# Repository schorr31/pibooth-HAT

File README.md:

# pibooth-HAT
A Raspberry Pi HAT for the pibooth application

### Images

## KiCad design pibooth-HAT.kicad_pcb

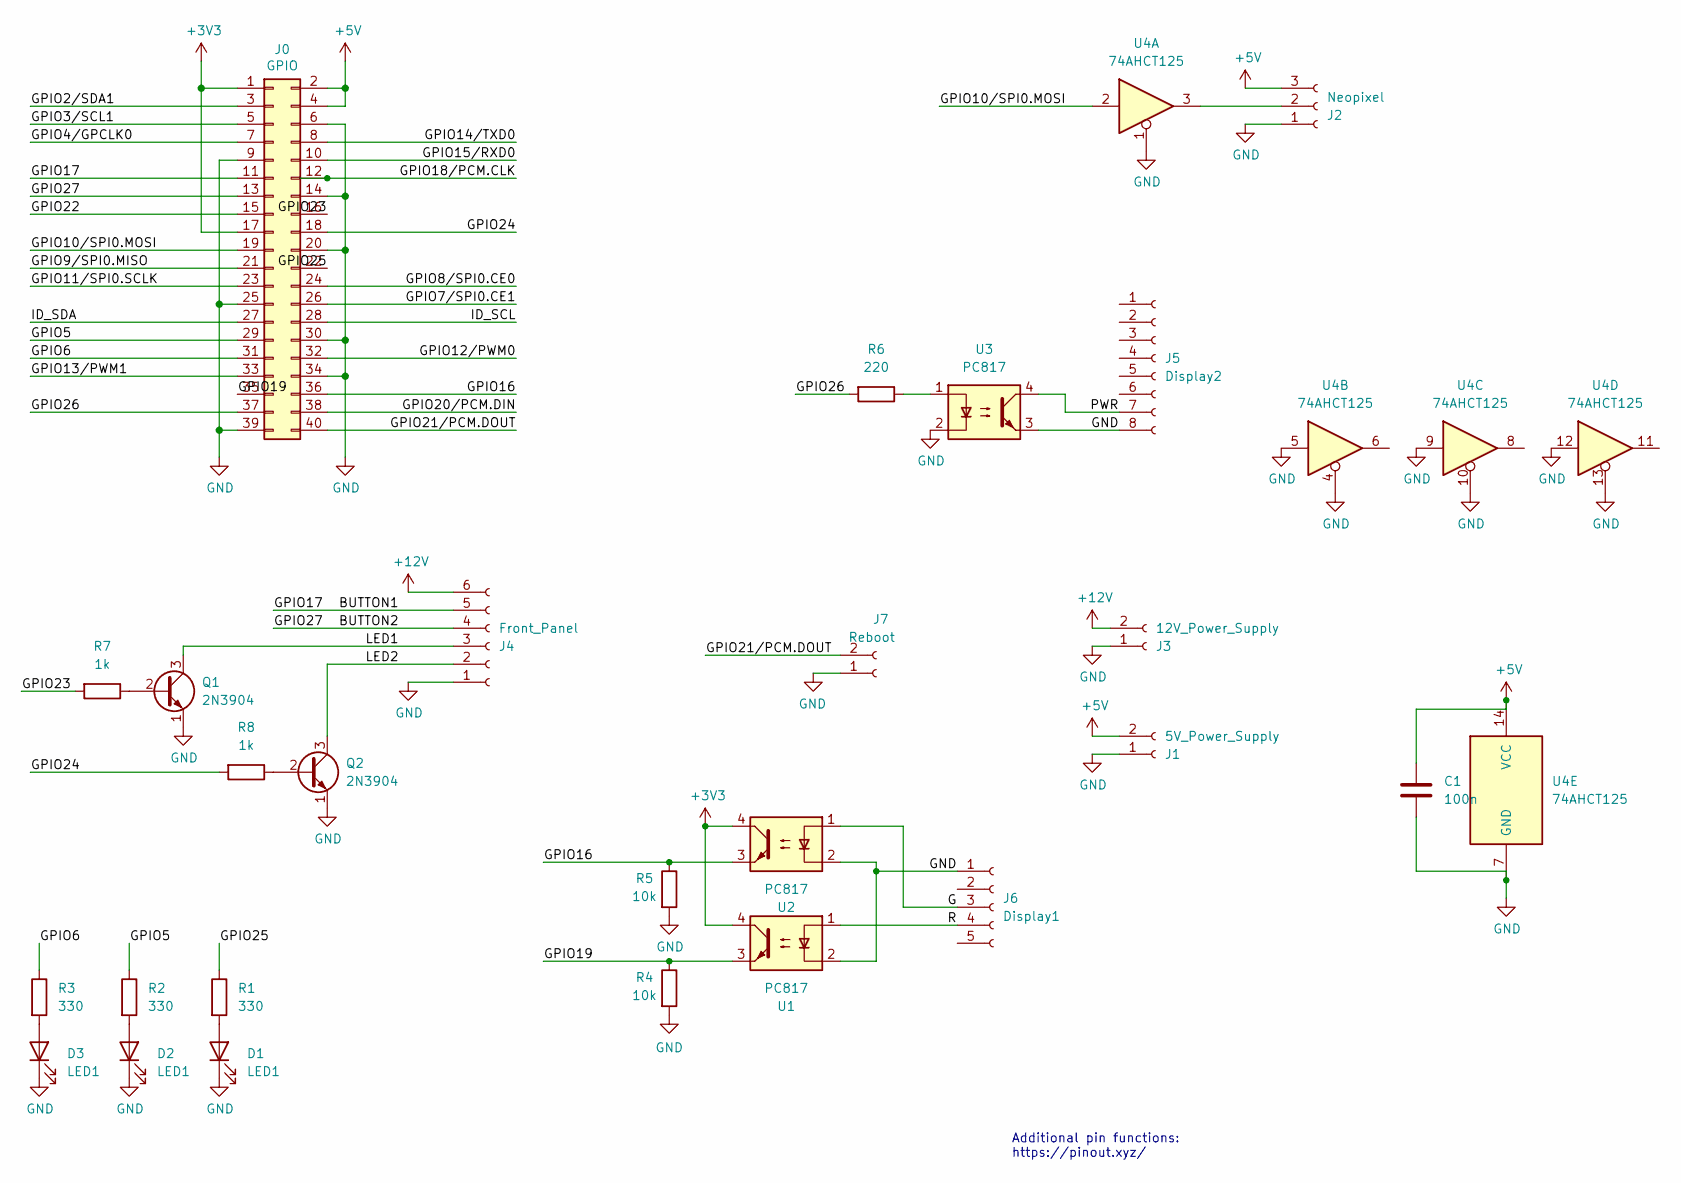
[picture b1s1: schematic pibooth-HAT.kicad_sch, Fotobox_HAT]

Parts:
C1: 100n; C_1206_3216Metric_Pad1.33x1.80mm_HandSolder
D1, D2, D3: LED1; LED_1206_3216Metric_Pad1.42x1.75mm_HandSolder
J0: GPIO; PinSocket_2x20_P2.54mm_Vertical
J1: 5V_Power_Supply; TerminalBlock_bornier-2_P5.08mm
J2: Neopixel; TerminalBlock_bornier-3_P5.08mm
J3: 12V_Power_Supply; TerminalBlock_bornier-2_P5.08mm
J4: Front_Panel; TerminalBlock_bornier-6_P5.08mm
J5: Display2; JST_PH_B8B-PH-K_1x08_P2.00mm_Vertical
J6: Display1; JST_PH_B5B-PH-K_1x05_P2.00mm_Vertical
J7: Reboot; JST_PH_B2B-PH-K_1x02_P2.00mm_Vertical
Q1, Q2: 2N3904; SOT-89-3_Handsoldering
R1, R2, R3: 330; R_1206_3216Metric_Pad1.30x1.75mm_HandSolder
R4, R5: 10k; R_1206_3216Metric_Pad1.30x1.75mm_HandSolder
R6: 220; R_1206_3216Metric_Pad1.30x1.75mm_HandSolder
R7, R8: 1k; R_1206_3216Metric_Pad1.30x1.75mm_HandSolder
U1, U2, U3: PC817; SMDIP-4_W7.62mm
U4: 74AHCT125; SOIC-14_3.9x8.7mm_P1.27mm

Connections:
+3V3: J0.1, J0.17, U1.4, U2.4
+5V: C1.1, J0.2, J0.4, J1.2, J2.3, U4.14 (VCC)
+12V: J3.2, J4.6
/BUTTON1: J0.11, J4.5
/BUTTON2: J0.13, J4.4
/G: J6.3, U2.1
/GPIO2/SDA1: J0.3
/GPIO3/SCL1: J0.5
/GPIO4/GPCLK0: J0.7
/GPIO5: J0.29, R2.1
/GPIO6: J0.31, R3.1
/GPIO7/SPI0.CE1: J0.26
/GPIO8/SPI0.CE0: J0.24
/GPIO9/SPI0.MISO: J0.21
/GPIO10/SPI0.MOSI: J0.19, U4.2
/GPIO11/SPI0.SCLK: J0.23
/GPIO12/PWM0: J0.32
/GPIO13/PWM1: J0.33
/GPIO14/TXD0: J0.8
/GPIO15/RXD0: J0.10
/GPIO16: J0.36, R5.1, U2.3
/GPIO18/PCM.CLK: J0.12
/GPIO19: J0.35, R4.1, U1.3
/GPIO20/PCM.DIN: J0.38
/GPIO22: J0.15
/GPIO23: J0.16, R7.2
/GPIO24: J0.18, R8.2
/GPIO25: J0.22, R1.1
/GPIO26: J0.37, R6.2
/ID_SCL: J0.28
/ID_SDA: J0.27
/LED1: J4.3, Q1.3 (C)
/LED2: J4.2, Q2.3 (C)
/PWR: J5.7, U3.4
/R: J6.4, U1.1
GND: C1.2, D1.1 (K), D2.1 (K), D3.1 (K), J0.6, J0.9, J0.14, J0.20, J0.25, J0.30, J0.34, J0.39, J1.1, J2.1, J3.1, J4.1, J5.8, J6.1, J7.1, Q1.1 (E), Q2.1 (E), R4.2, R5.2, U1.2, U2.2, U3.2, U3.3, U4.1, U4.4, U4.5, U4.7 (GND), U4.9, U4.10, U4.12, U4.13
unnamed: D1.2 (A), R1.2
unnamed: D2.2 (A), R2.2
unnamed: D3.2 (A), R3.2
unnamed: J2.2, U4.3
unnamed: Q1.2 (B), R7.1
unnamed: Q2.2 (B), R8.1
unnamed: R6.1, U3.1

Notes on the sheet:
Additional pin functions: https://pinout.xyz/

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
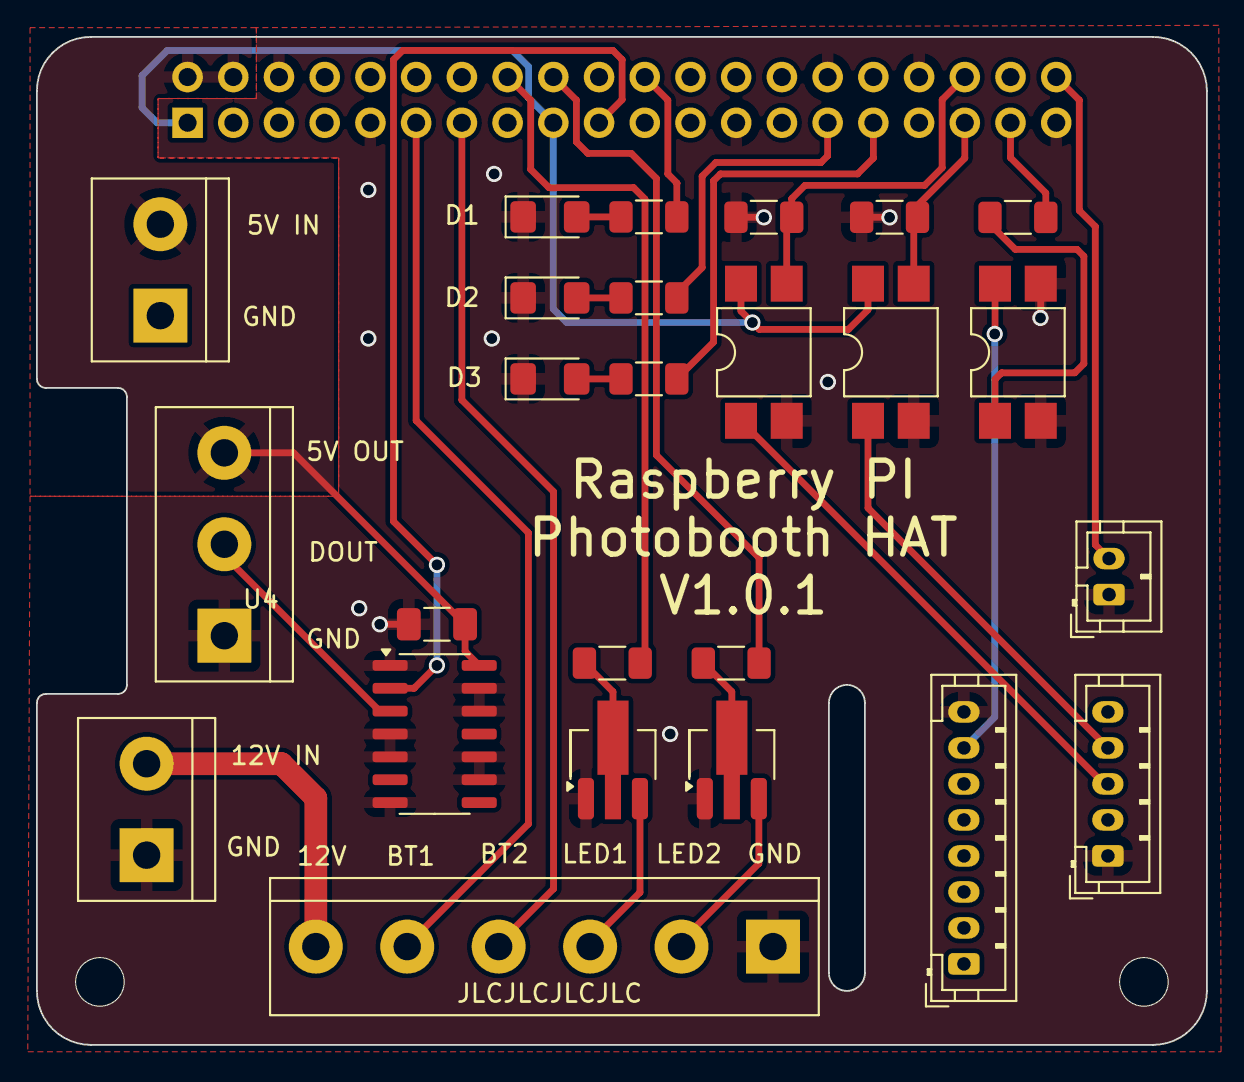
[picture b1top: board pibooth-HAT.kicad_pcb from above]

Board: 2 copper layers, 65.0 x 56.0 mm, 28 parts (1 on the bottom side), 28 nets.

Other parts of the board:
MH3, MH4: MountingHole_2.7mm_M2.5

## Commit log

2024-09-11 Added first PCB version
2024-09-11 added picturer generation workflow
2024-09-11 Fixed workflow
2024-09-11 Readme image fix
